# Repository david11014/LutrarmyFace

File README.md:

# LutrarmyMic microphone circuit

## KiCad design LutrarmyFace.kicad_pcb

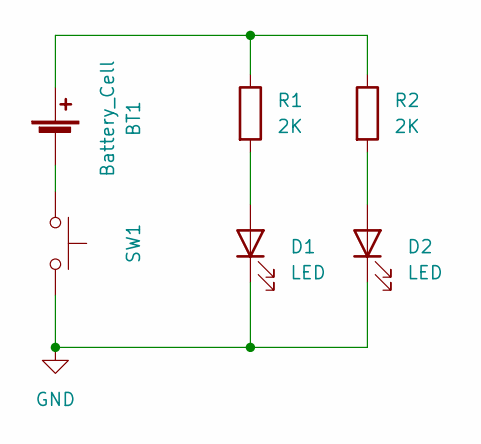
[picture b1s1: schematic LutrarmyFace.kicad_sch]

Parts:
BT1: Battery_Cell; BatteryHolder_Keystone_1060_1x2032
D1, D2: LED; LED_0805_2012Metric_Pad1.15x1.40mm_HandSolder
R1, R2: 2K; R_0805_2012Metric_Pad1.20x1.40mm_HandSolder
SW1: SW_Push; SW_SPST_TL3342

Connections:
GND: D1.1 (K), D2.1 (K), SW1.2
unnamed: BT1.1 (+), R1.1, R2.1
unnamed: BT1.2 (-), SW1.1
unnamed: D1.2 (A), R1.2
unnamed: D2.2 (A), R2.2

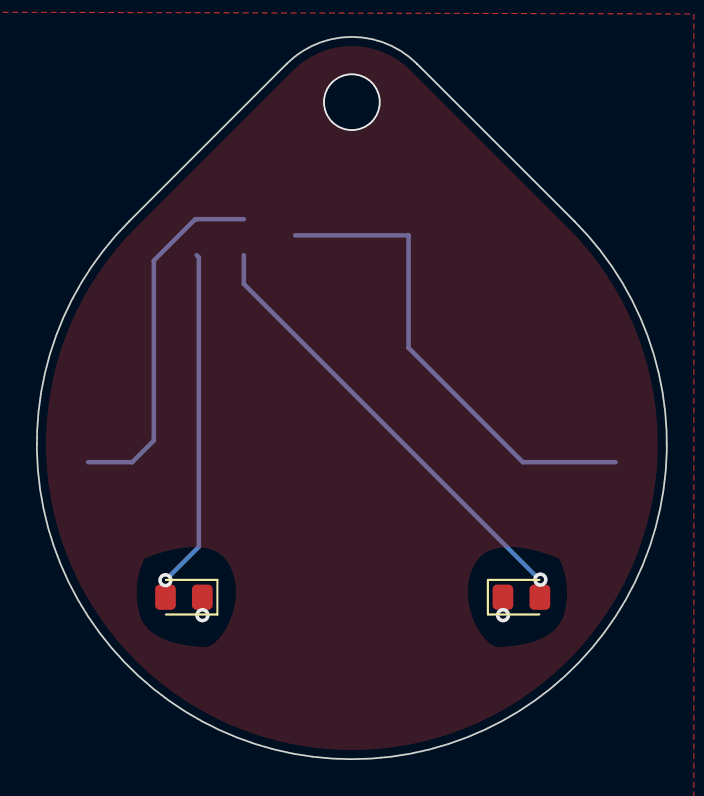
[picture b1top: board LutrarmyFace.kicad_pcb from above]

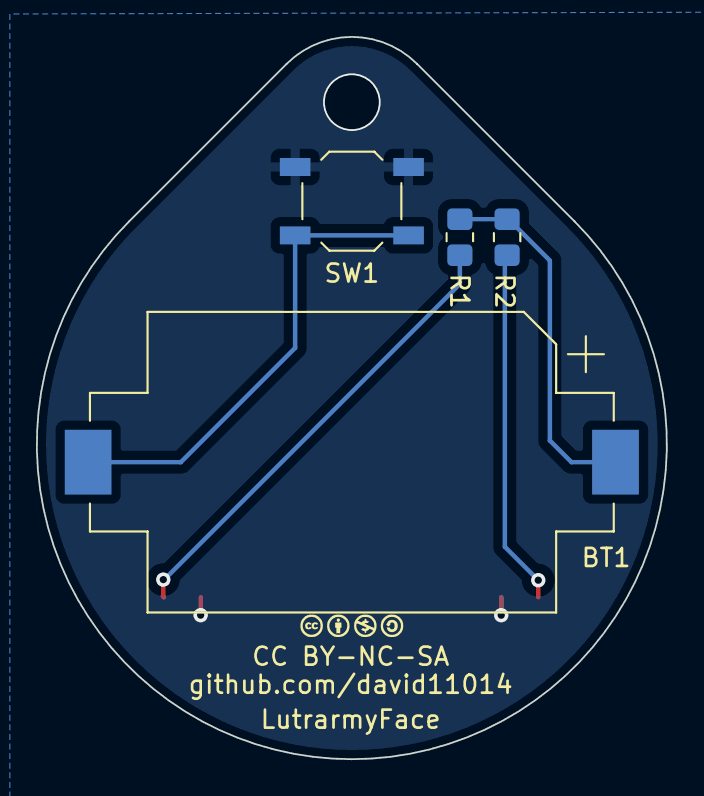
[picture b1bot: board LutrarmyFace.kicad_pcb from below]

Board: 2 copper layers, 35.0 x 40.1 mm, 7 parts (5 on the bottom side), 5 nets.

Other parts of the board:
LutrarmyFace: CC-BY-NC-SA

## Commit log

2023-12-23 init commit
2023-12-23 Add README and LICENSE
